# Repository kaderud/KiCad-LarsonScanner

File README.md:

# Larson Scanner
_Demonstration board for soldering a Larson Scanner_

These are the source files for the KiCad project "Larson Scanner"

If you want to make one of these for yourself you can use this design as it is or alter it and make it better.

## Production

The PCBs were made at [JLCPCB](https://jlcpcb.com/)

The **Gerber** files in the _Production_ directory are the identical files used to produce the PCBs.

## Pictures

Here are some images of the v1.0 release board:

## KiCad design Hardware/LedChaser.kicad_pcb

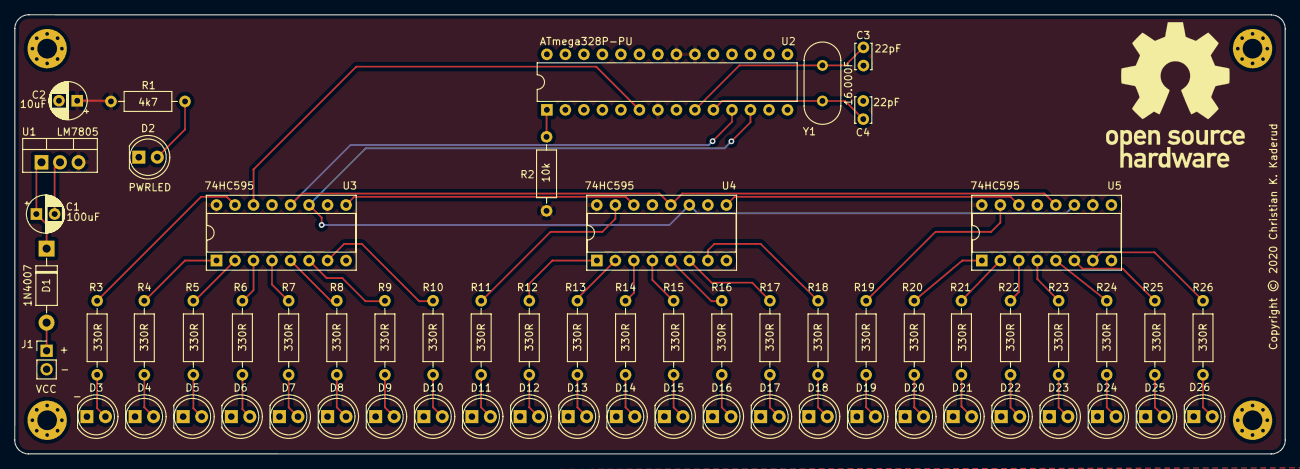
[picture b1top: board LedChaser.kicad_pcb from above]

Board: 2 copper layers, 174.4 x 60.3 mm, 67 parts (0 on the bottom side), 61 nets.

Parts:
C1: 100uF; CP_Radial_D5.0mm_P2.50mm
C2: 10uF; CP_Radial_D5.0mm_P2.50mm
C3, C4: 22pF; C_Disc_D3.4mm_W2.1mm_P2.50mm
D1: 1N4007; D_DO-41_SOD81_P10.16mm_Horizontal
D2, D3, D4, D5, D6, D7, D8, D9, D10, D11, D12, D13, D14, D15, D16, D17, D18, D19, D20, D21, D22, D23, D24, D25, D26: LED; LED_D5.0mm
H1, H2, H3, H4: MountingHole_Pad; MountingHole_2.7mm_M2.5_Pad_Via
J1: VCC; PinHeader_1x02_P2.54mm_Vertical
R1: 4k7; R_Axial_DIN0207_L6.3mm_D2.5mm_P10.16mm_Horizontal
R2: 10k; R_Axial_DIN0207_L6.3mm_D2.5mm_P10.16mm_Horizontal
R3, R4, R5, R6, R7, R8, R9, R10, R11, R12, R13, R14, R15, R16, R17, R18, R19, R20, R21, R22, R23, R24, R25, R26: 330R; R_Axial_DIN0207_L6.3mm_D2.5mm_P10.16mm_Horizontal
U1: LM7805; TO-220-3_Vertical
U2: ATmega328P-PU; DIP-28_W7.62mm
U3, U4, U5: 74HC595; DIP-16_W7.62mm_Socket
Y1: 16.000F; Crystal_HC49-U_Vertical

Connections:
+5V: C2.1, R1.2, R2.1, U1.3, U2.7, U2.20, U2.21, U3.10, U3.16, U4.10, U4.16, U5.10, U5.16
/RESET: R2.2, U2.1
GND: C1.2, C2.2, C3.1, C4.2, D2.1, D3.1, D4.1, D5.1, D6.1, D7.1, D8.1, D9.1, D10.1, D11.1, D12.1, D13.1, D14.1, D15.1, D16.1, D17.1, D18.1, D19.1, D20.1, D21.1, D22.1, D23.1, D24.1, D25.1, D26.1, H1.1, H2.1, H3.1, H4.1, J1.2, U1.2, U2.8, U2.22, U3.8, U3.13, U4.8, U4.13, U5.8, U5.13
LED01: R3.1, U3.15
LED02: R4.1, U3.1
LED03: R5.1, U3.2
LED04: R6.1, U3.3
LED05: R7.1, U3.4
LED06: R8.1, U3.5
LED07: R9.1, U3.6
LED08: R10.1, U3.7
LED09: R11.1, U4.15
LED10: R12.1, U4.1
LED11: R13.1, U4.2
LED12: R14.1, U4.3
LED13: R15.1, U4.4
LED14: R16.1, U4.5
LED15: R17.1, U4.6
LED16: R18.1, U4.7
LED17: R19.1, U5.15
LED18: R20.1, U5.1
LED19: R21.1, U5.2
LED20: R22.1, U5.3
LED21: R23.1, U5.4
LED22: R24.1, U5.5
LED23: R25.1, U5.6
LED24: R26.1, U5.7
unnamed: C1.1, D1.1, U1.1
unnamed: D2.2, R1.1
unnamed: D3.2, R3.2
unnamed: D4.2, R4.2
unnamed: D5.2, R5.2
unnamed: D6.2, R6.2
unnamed: D7.2, R7.2
unnamed: D8.2, R8.2
unnamed: D9.2, R9.2
unnamed: D10.2, R10.2
unnamed: D11.2, R11.2
unnamed: D12.2, R12.2
unnamed: D13.2, R13.2
unnamed: D14.2, R14.2
unnamed: D15.2, R15.2
unnamed: D16.2, R16.2
unnamed: D17.2, R17.2
unnamed: D18.2, R18.2
unnamed: D19.2, R19.2
unnamed: D20.2, R20.2
unnamed: D21.2, R21.2
unnamed: D22.2, R22.2
unnamed: D23.2, R23.2
unnamed: D24.2, R24.2
unnamed: D25.2, R25.2
unnamed: D26.2, R26.2
RCLK: U2.11, U3.12, U4.12, U5.12
SER: U2.6, U3.14
SEROUT1: U3.9, U4.14
SEROUT2: U4.9, U5.14
SRCLK: U2.12, U3.11, U4.11, U5.11
VCC: D1.2, J1.1
XTAL1: C3.2, U2.9, Y1.1
XTAL2: C4.1, U2.10, Y1.2

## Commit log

2020-11-06 CERN Open Hardware Licence v1.2
2020-11-06 Schematic & Screenshots
2020-11-06 KiCad project files
2020-11-06 gerbers
2020-11-07 Firmware source
2020-11-07 Firmware file & helper

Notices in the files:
Hardware/LedChaser.kicad_pcb:
Copyright © 2020 Christian K. Kaderud
